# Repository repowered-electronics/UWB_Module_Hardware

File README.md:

These are the hardware files for our DWM1000 based localization module.

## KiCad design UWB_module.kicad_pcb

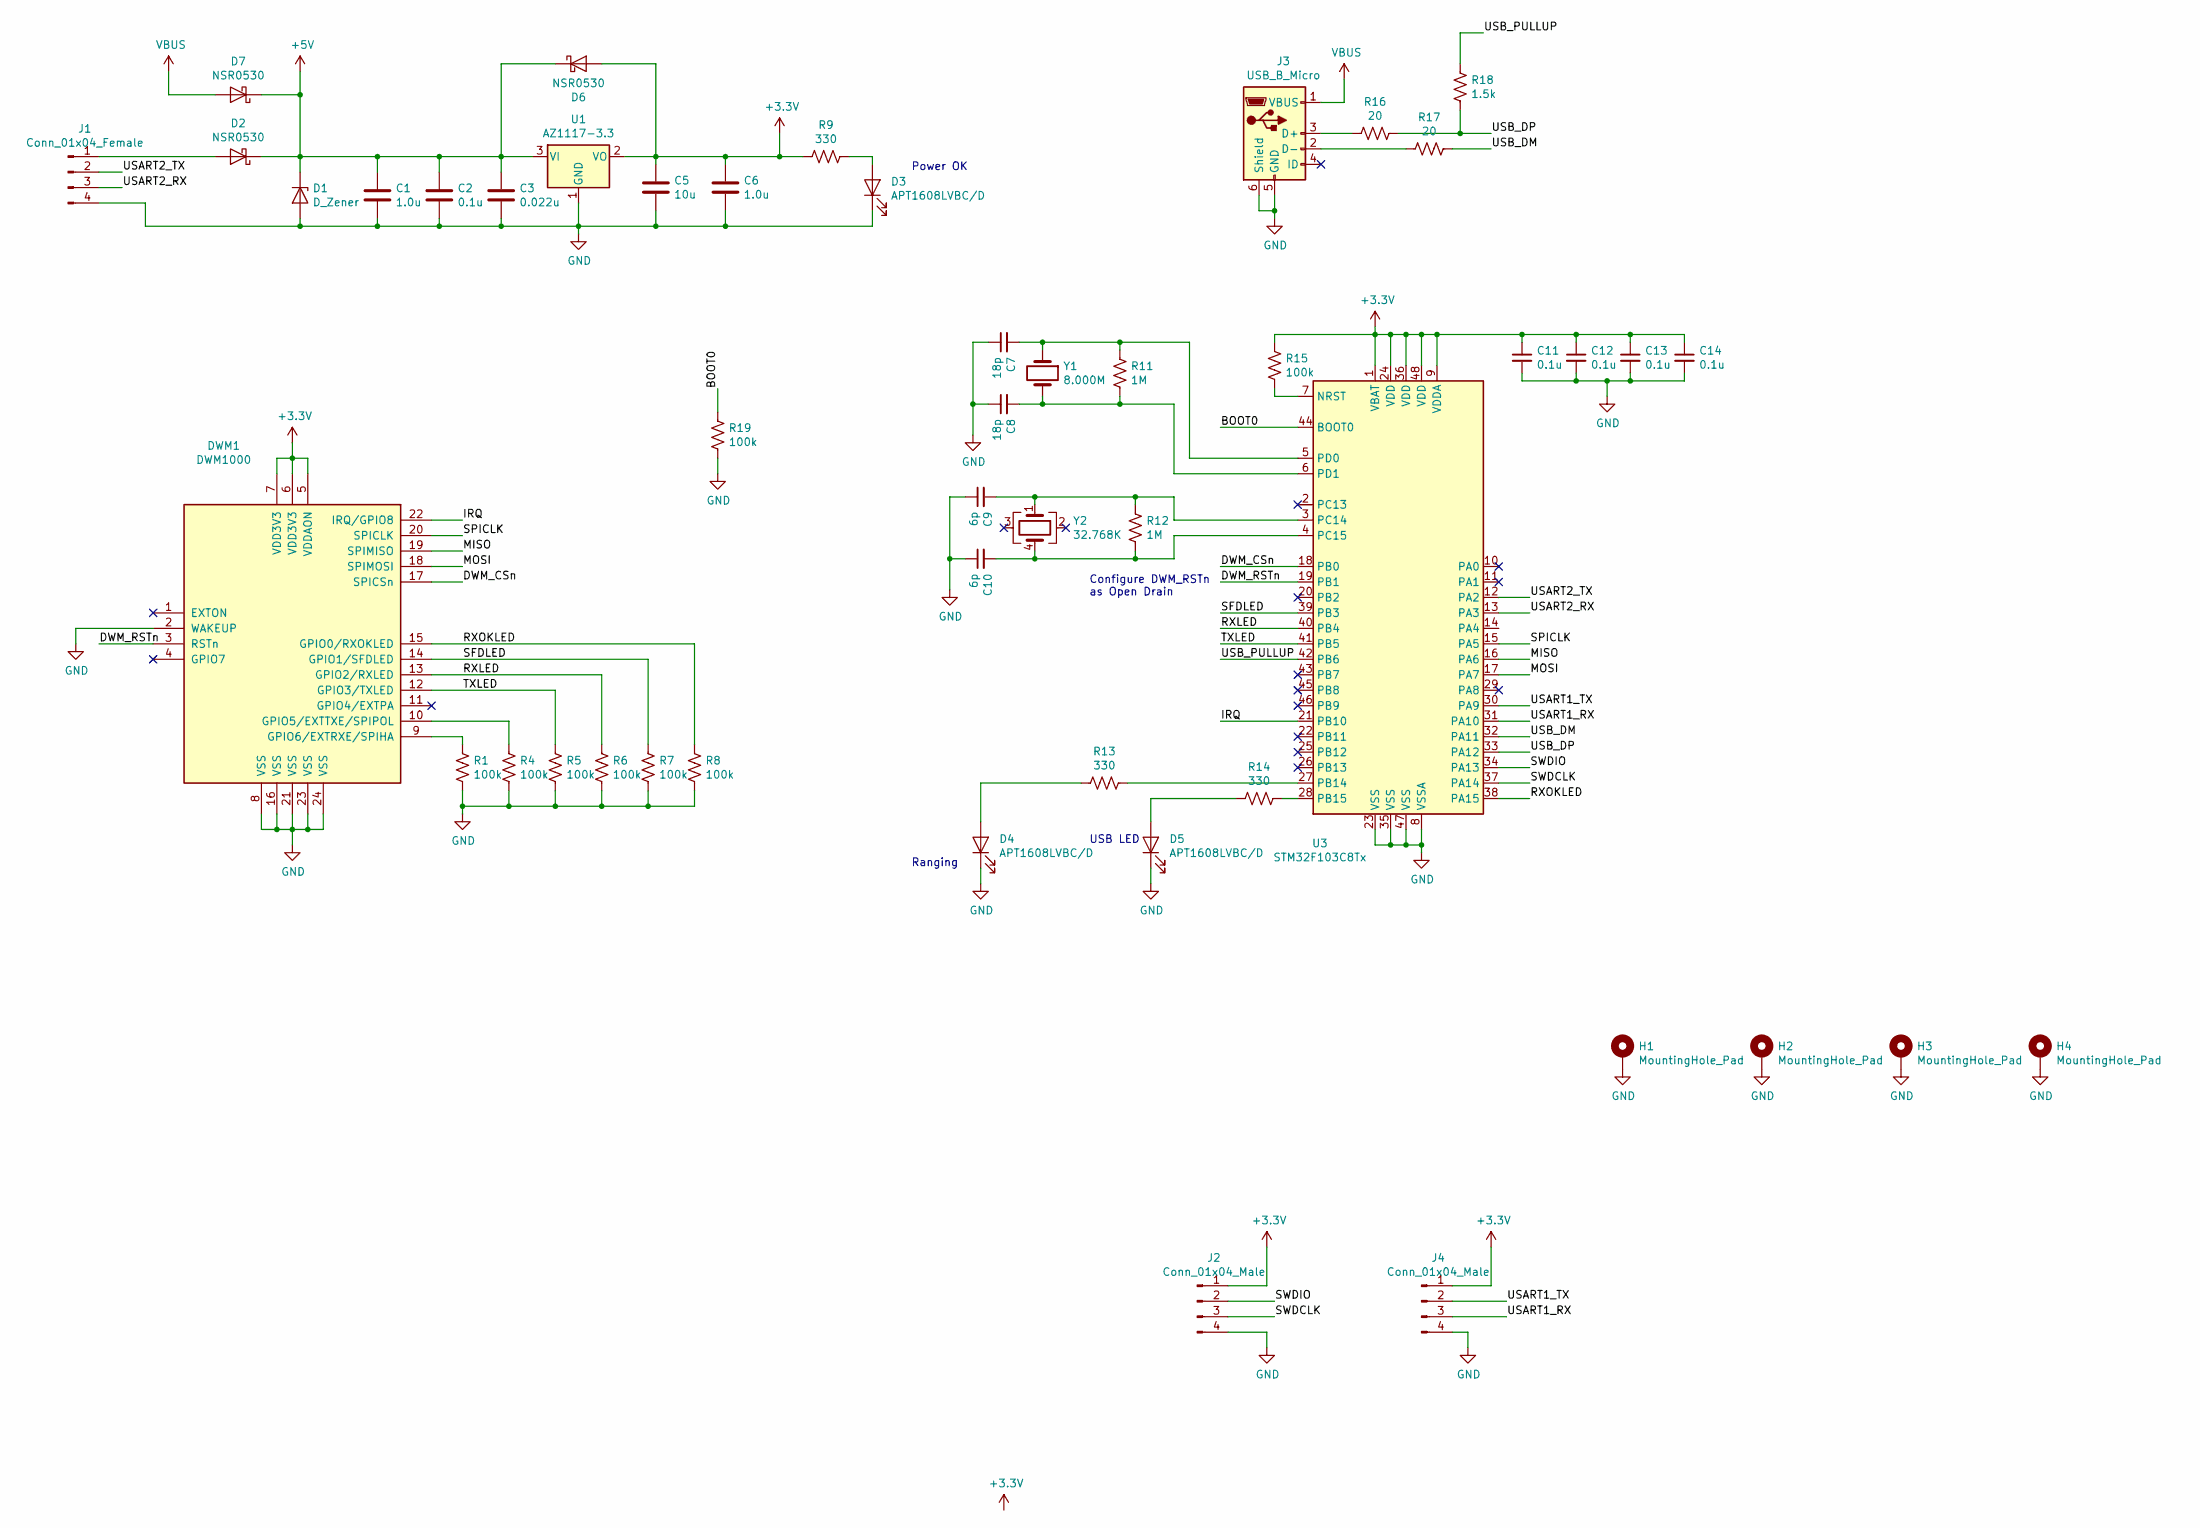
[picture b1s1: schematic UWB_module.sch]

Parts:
C1, C6: 1.0u; C_0805_2012Metric
C2, C11, C12, C13, C14: 0.1u; C_0603_1608Metric
C3: 0.022u; C_0603_1608Metric
C5: 10u; C_0805_2012Metric
C7, C8: 18p; C_0603_1608Metric
C9, C10: 6p; C_0603_1608Metric
D1: D_Zener; D_SOD-323
D2, D6, D7: NSR0530; D_SOD-323
D3, D4, D5: APT1608LVBC/D; LED_0603_1608Metric
DWM1: DWM1000
H1, H2, H3, H4: MountingHole_Pad; MountingHole_3.5mm_Pad
J1: Conn_01x04_Female; TerminalBlock_Phoenix_PTSA-1,5-4-3.5-H_1x04_P3.50mm_Horizon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
J2, J4: Conn_01x04_Male; PinHeader_1x04_P2.54mm_Vertical
J3: USB_B_Micro; USB_Micro-B_Amphenol_10103594-0001LF_Horizontal
R1, R4, R5, R6, R7, R8, R15, R19: 100k; R_0603_1608Metric
R9, R13, R14: 330; R_0603_1608Metric
R11, R12: 1M; R_0603_1608Metric
R16, R17: 20; R_0603_1608Metric
R18: 1.5k; R_0603_1608Metric
U1: AZ1117-3.3; SOT-89-3
U3: STM32F103C8Tx; LQFP-48_7x7mm_P0.5mm
Y1: 8.000M; XTAL_ABLS-8.000MHZ-B2-T
Y2: 32.768K; XTAL_ABS25-32.768KHZ-6-T

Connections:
+3V3: C5.1, C6.1, C11.1, C12.1, C13.1, C14.1, D6.2 (A), DWM1.5 (VDDAON), DWM1.6 (VDD3V3), DWM1.7 (VDD3V3), J2.1, J4.1, R9.2, R15.1, U1.2 (VO), U3.1 (VBAT), U3.9 (VDDA), U3.24 (VDD), U3.36 (VDD), U3.48 (VDD)
+5V: C1.1, C2.1, C3.1, D1.1 (K), D2.1 (K), D6.1 (K), D7.1 (K), U1.3 (VI)
/BOOT0: R19.1, U3.44 (BOOT0)
/DWM_CSn: DWM1.17 (SPICSn), U3.18 (PB0)
/DWM_RSTn: DWM1.3 (RSTn), U3.19 (PB1)
/IRQ: DWM1.22 (IRQ/GPIO8), U3.21 (PB10)
/MISO: DWM1.19 (SPIMISO), U3.16 (PA6)
/MOSI: DWM1.18 (SPIMOSI), U3.17 (PA7)
/RXLED: DWM1.13 (GPIO2/RXLED), R6.1, U3.40 (PB4)
/RXOKLED: DWM1.15 (GPIO0/RXOKLED), R8.1, U3.38 (PA15)
/SFDLED: DWM1.14 (GPIO1/SFDLED), R7.1, U3.39 (PB3)
/SPICLK: DWM1.20 (SPICLK), U3.15 (PA5)
/SWDCLK: J2.3, U3.37 (PA14)
/SWDIO: J2.2, U3.34 (PA13)
/TXLED: DWM1.12 (GPIO3/TXLED), R5.1, U3.41 (PB5)
/USART1_RX: J4.3, U3.31 (PA10)
/USART1_TX: J4.2, U3.30 (PA9)
/USART2_RX: J1.3, U3.13 (PA3)
/USART2_TX: J1.2, U3.12 (PA2)
/USB_DM: R17.1, U3.32 (PA11)
/USB_DP: R16.1, R18.2, U3.33 (PA12)
/USB_PULLUP: R18.1, U3.42 (PB6)
GND: C1.2, C2.2, C3.2, C5.2, C6.2, C7.1, C8.1, C9.1, C10.1, C11.2, C12.2, C13.2, C14.2, D1.2 (A), D3.1 (K), D4.1 (K), D5.1 (K), DWM1.2 (WAKEUP), DWM1.8 (VSS), DWM1.16 (VSS), DWM1.21 (VSS), DWM1.23 (VSS), DWM1.24 (VSS), H1.1, H2.1, H3.1, H4.1, J1.4, J2.4, J3.5 (GND), J3.6 (Shield), J4.4, R1.2, R4.2, R5.2, R6.2, R7.2, R8.2, R19.2, U1.1 (GND), U3.8 (VSSA), U3.23 (VSS), U3.35 (VSS), U3.47 (VSS)
unnamed: C7.2, R11.1, U3.5 (PD0), Y1.1
unnamed: C8.2, R11.2, U3.6 (PD1), Y1.2
unnamed: C9.2, R12.1, U3.3 (PC14), Y2.1
unnamed: C10.2, R12.2, U3.4 (PC15), Y2.4
unnamed: D2.2 (A), J1.1
unnamed: D3.2 (A), R9.1
unnamed: D4.2 (A), R13.2
unnamed: D5.2 (A), R14.2
unnamed: DWM1.9 (GPIO6/EXTRXE/SPIHA), R1.1
unnamed: DWM1.10 (GPIO5/EXTTXE/SPIPOL), R4.1
unnamed: J3.2 (D-), R17.2
unnamed: J3.3 (D+), R16.2
unnamed: R13.1, U3.27 (PB14)
unnamed: R14.1, U3.28 (PB15)
unnamed: R15.2, U3.7 (NRST)
VBUS: D7.2 (A), J3.1 (VBUS)

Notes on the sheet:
Power OK
Configure DWM_RSTn as Open Drain
USB LED
Ranging

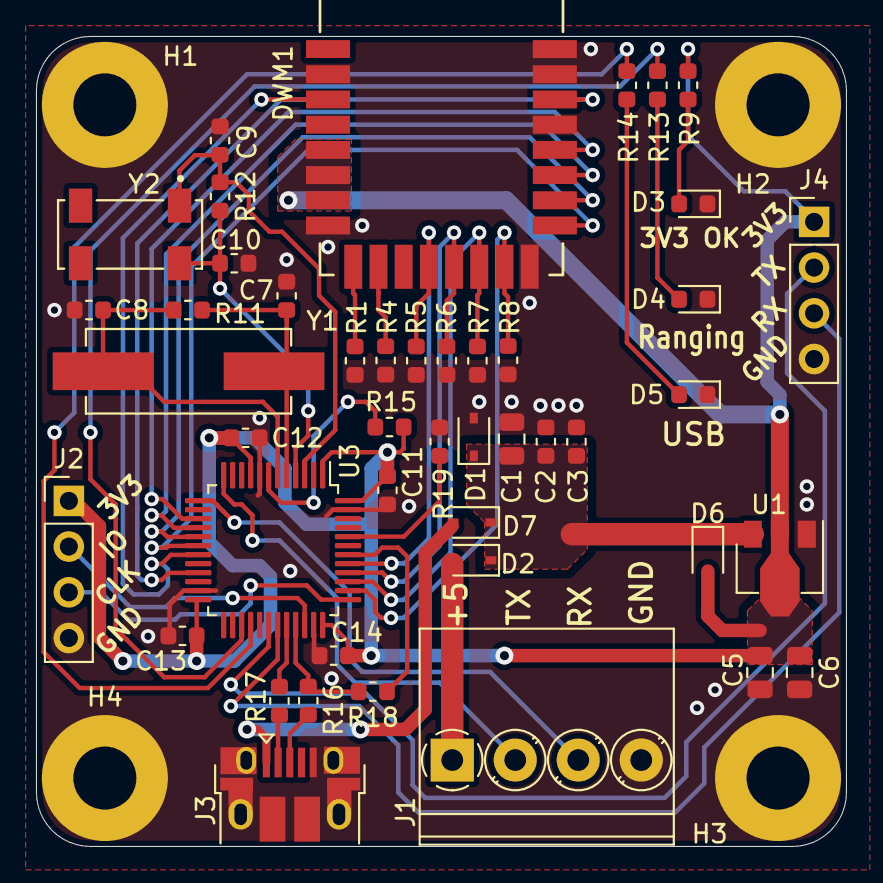
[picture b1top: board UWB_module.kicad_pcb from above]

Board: 2 copper layers, 45.0 x 45.0 mm, 49 parts (0 on the bottom side), 39 nets.

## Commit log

2019-08-20 Initial commit, schematic and PCB are incomplete
2019-08-20 Add README
2019-08-20 Add gitattributes file
2019-08-20 Complete initial schematic and layout
2019-08-23 Add most up-to-date PCB and STEP file

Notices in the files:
UWB_module.kicad_pcb:
(c) 2019 Repowered Robotics
